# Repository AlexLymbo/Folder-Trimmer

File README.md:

# Folder Trimmer 📁✂️
## Description 📝
Folder Trimmer is a tool designed to help clean up unnecessary files from folders, specifically targeting KiCad files for now. Useful for saving space from autogenerated clutter and preparing projects for distribution. 

## Current Functionality ⚙️
Trimming KiCad Files: The script removes specific unwanted files from a KiCad project folder based on predefined patterns.
Copying Files: It copies files from the target folder to a new folder called "trim," excluding files that match the trim patterns.

## Usage 🚀
1. Clone the Repository
```
git clone https://github.com/yourusername/folder-trimmer.git
cd folder-trimmer
```
2. Run the Script
```
python folder_trimmer.py
```
You will be prompted to enter the path to the target folder. The script will then process this folder, copying files to a "trim" folder and removing any files that match the trim patterns.

## Future Plans 🔮
- GUI Development: Adding a graphical user interface to make the tool more user-friendly.
- Support for Other Formats: Extending functionality to handle different types of files and formats, such as Matlab/Simulink and Altium.

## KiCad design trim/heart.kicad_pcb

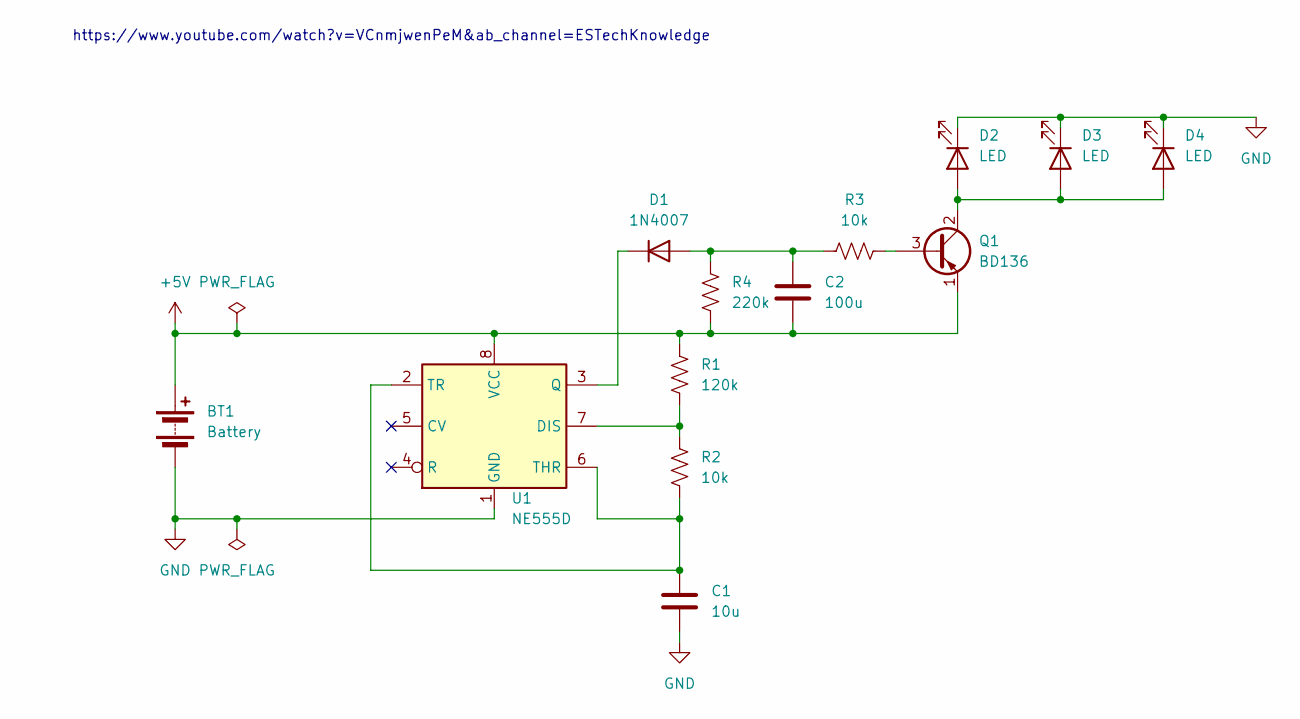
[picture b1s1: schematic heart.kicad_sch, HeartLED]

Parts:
BT1: Battery; 2479PCB_37P49X52P63_KEY
C1: 10u; C_0603_1608Metric_Pad1.08x0.95mm_HandSolder
C2: 100u; C_0603_1608Metric_Pad1.08x0.95mm_HandSolder
D1: 1N4007; D_DO-41_SOD81_P10.16mm_Horizontal
D2, D3, D4: LED; LED_D5.0mm_FlatTop
Q1: BD136; TO-126-3_Vertical
R1: 120k; R_0603_1608Metric_Pad0.98x0.95mm_HandSolder
R2, R3: 10k; R_0603_1608Metric_Pad0.98x0.95mm_HandSolder
R4: 220k; R_0603_1608Metric_Pad0.98x0.95mm_HandSolder
U1: NE555D; SOIC-8_3.9x4.9mm_P1.27mm

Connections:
+5V: BT1.1 (+), C2.1, Q1.1 (E), R1.1, R4.2, U1.8 (VCC)
GND: BT1.2 (-), C1.1, D2.1 (K), D3.1 (K), D4.1 (K), U1.1 (GND)
unnamed: C2.2, D1.2 (A), R3.1, R4.1
unnamed: D1.1 (K), U1.3 (Q)
unnamed: D2.2 (A), D3.2 (A), D4.2 (A), Q1.2 (C)
unnamed: Q1.3 (B), R3.2
unnamed: R1.2, R2.1, U1.7 (DIS)
unnamed: C1.2, R2.2, U1.2 (TR), U1.6 (THR)

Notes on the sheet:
https://www.youtube.com/watch?v=VCnmjwenPeM&ab_channel=ESTechKnowledge

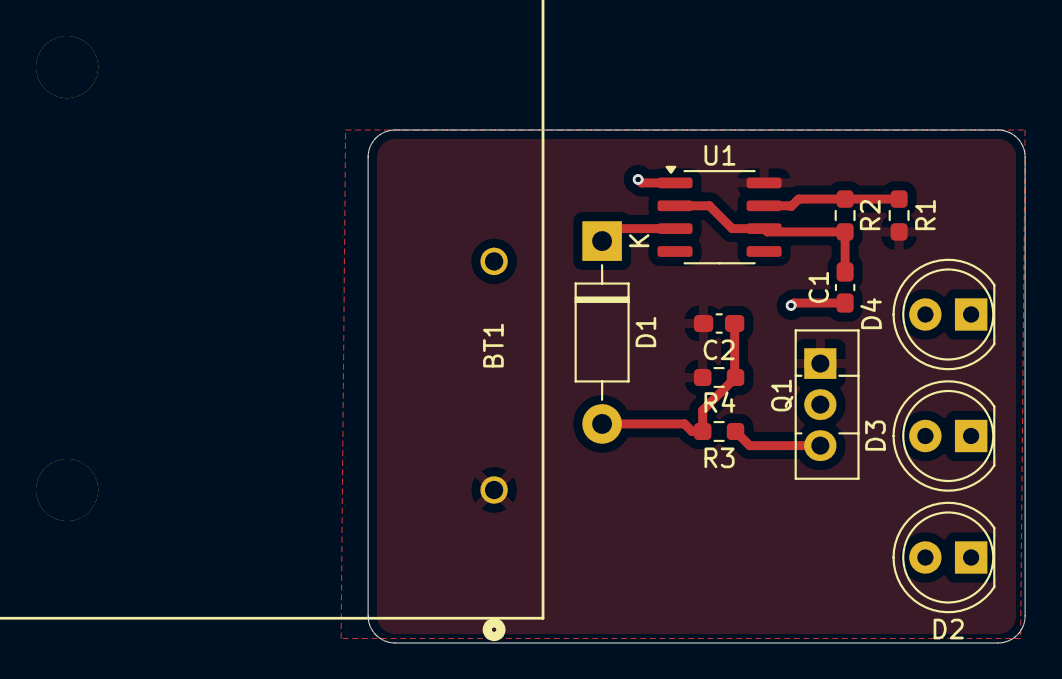
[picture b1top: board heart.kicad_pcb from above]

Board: 2 copper layers, 36.5 x 28.5 mm, 13 parts (0 on the bottom side), 8 nets.

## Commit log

2024-09-06 init files trimmer for kicad
2024-09-06 working for kicad folders. will add options later
